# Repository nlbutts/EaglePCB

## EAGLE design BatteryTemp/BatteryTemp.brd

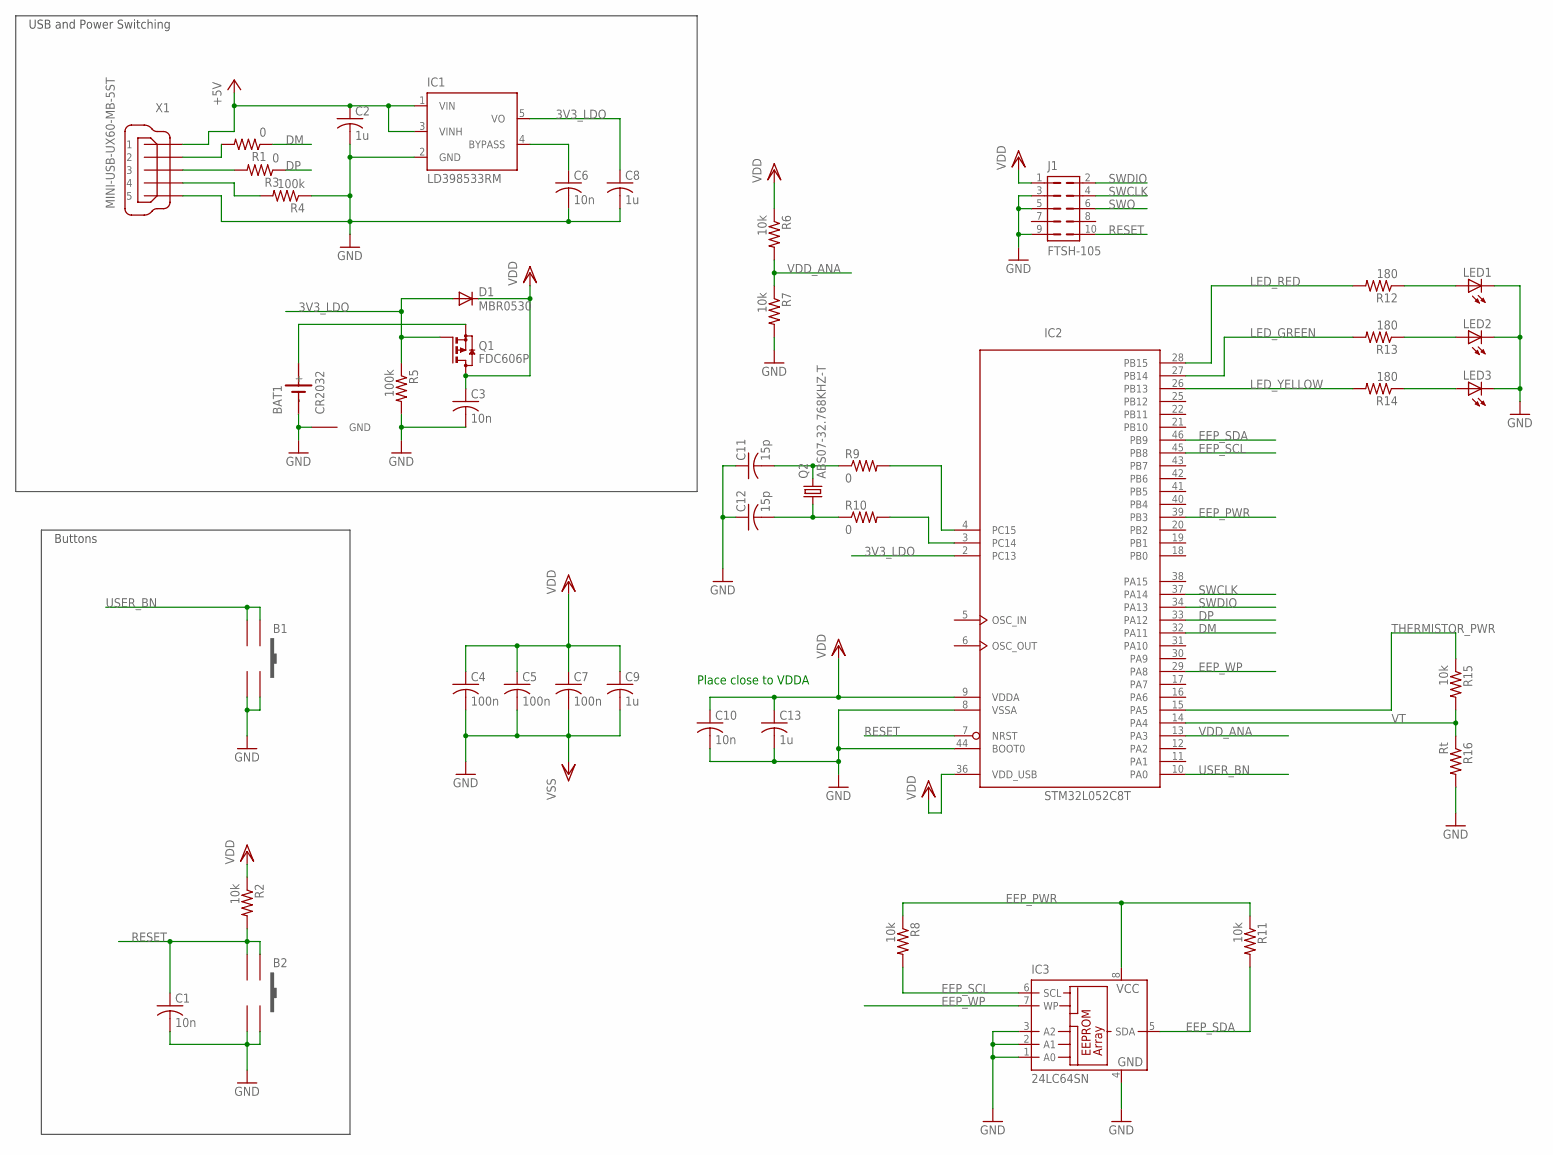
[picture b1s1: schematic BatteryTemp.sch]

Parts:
B1, B2: PTS525SM10SMTR; DIGIKEY CKN9104CT-ND
BAT1: CR2032; COIN_CELL; DIGIKEY BK-913-ND
C1, C3, C6: 10n; C0603
C2, C8, C9, C13: 1u; C0603
C4, C5, C7: 100n; C0603
C10: 10n; C0603; DIGIKEY 490-1512-1-ND
C11, C12: 15p; C0603
D1: MBR0530; SOD-123_MINI-SMA; DIGIKEY MBR0530TPMSCT-ND
IC1: LD398533RM; SOT23-5L; DIGIKEY 497-3504-1-ND
IC2: STM32L052C8T; LQFP48; DIGIKEY 497-14903-ND
IC3: 24LC64SN; SO-08
J1: FTSH-105; FTSH-105-01-XXX-DV-K; DIGIKEY SAM1161-50-ND
LED1: LEDCHIP-LED0603; CHIP-LED0603; DIGIKEY 475-2506-1-ND
LED2: LEDCHIP-LED0603; CHIP-LED0603; DIGIKEY 475-2709-1-ND
LED3: LEDCHIP-LED0603; CHIP-LED0603; DIGIKEY 475-1196-1-ND
Q1: FDC606P; SOT-23-6; DIGIKEY FDC606PCT-ND
Q2: ABS07-32.768KHZ-T; 2-SMD
R1, R3: 0; R0603; DIGIKEY P0.0GCT-ND
R2, R8, R11, R15: 10k; R0603
R4: 100k; R0603; DIGIKEY P100KGCT-ND
R5: 100k; R0603
R6, R7: 10k; R0603; DIGIKEY P10KYCT-ND
R9, R10: 0; R0603
R12: 180; R0603; DIGIKEY P180GCT-ND
R13, R14: 180; R0603
R16: Rt; R0603; DIGIKEY 490-2436-1-ND
T1: GND_LUG; GND_PAD
X1: MINI-USB-UX60-MB-5ST; UX60-MB-5ST; DIGIKEY H2959CT-ND

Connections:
3V3_LDO: C8.1, D1.A, IC1.5 (VO), IC2.2 (PC13), Q1.3 (G), R5.1
+5V: C2.1, IC1.1 (VIN), IC1.3 (VINH), X1.1
DM: IC2.32 (PA11), R1.1
DP: IC2.33 (PA12), R3.1
EEP_PWR: IC2.39 (PB3), IC3.8 (VCC), R8.1, R11.1
EEP_SCL: IC2.45 (PB8), IC3.6 (SCL), R8.2
EEP_SDA: IC2.46 (PB9), IC3.5 (SDA), R11.2
EEP_WP: IC2.29 (PA8), IC3.7 (WP)
GND: B1.3, B1.4, B2.3, B2.4, BAT1.GND1 (-), C1.2, C2.2, C3.2, C4.2, C5.2, C6.2, C7.2, C8.2, C9.2, C10.2, C11.1, C12.1, C13.2, IC1.2 (GND), IC2.8 (VSSA), IC2.23 (VSS), IC2.35 (VSS), IC2.44 (BOOT0), IC2.47 (VSS), IC3.1 (A0), IC3.2 (A1), IC3.3 (A2), IC3.4 (GND), J1.3, J1.5, J1.9, LED1.C, LED2.C, LED3.C, R4.1, R5.2, R7.2, R16.2, T1.P$1, X1.5
LED_GREEN: IC2.27 (PB14), R13.2
LED_RED: IC2.28 (PB15), R12.2
LED_YELLOW: IC2.26 (PB13), R14.2
unnamed: R1.2, X1.2
unnamed: R3.2, X1.3
unnamed: R4.2, X1.4
unnamed: BAT1.VPLUS1 (+), BAT1.VPLUS2 (+), Q1.4 (S)
unnamed: LED1.A, R12.1
unnamed: C6.1, IC1.4 (BYPASS)
unnamed: C11.2, Q2.P$2 (2), R9.1
unnamed: LED2.A, R13.1
unnamed: LED3.A, R14.1
unnamed: C12.2, Q2.P$1 (1), R10.1
unnamed: IC2.4 (PC15), R9.2
unnamed: IC2.3 (PC14), R10.2
RESET: B2.1, B2.2, C1.1, IC2.7 (NRST), J1.10, R2.2
SWCLK: IC2.37 (PA14), J1.4
SWDIO: IC2.34 (PA13), J1.2
SWO: J1.6
THERMISTOR_PWR: IC2.15 (PA5), R15.1
USER_BN: B1.1, B1.2, IC2.10 (PA0)
VDD: C3.1, C4.1, C5.1, C7.1, C9.1, C10.1, C13.1, D1.C, IC2.1 (VDD), IC2.9 (VDDA), IC2.24 (VDD), IC2.36 (VDD_USB), IC2.48 (VDD), J1.1, Q1.1 (D), Q1.2 (D), Q1.5 (D), Q1.6 (D), R2.1, R6.1
VDD_ANA: IC2.13 (PA3), R6.2, R7.1
VT: IC2.14 (PA4), R15.2, R16.1

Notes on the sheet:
Buttons
USB and Power Switching
Place close to VDDA

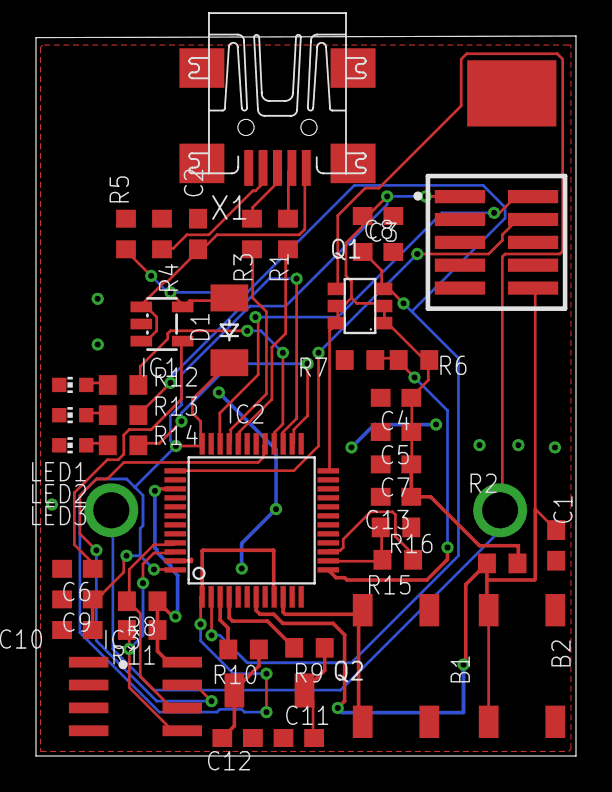
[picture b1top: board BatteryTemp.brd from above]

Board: 2 copper layers, 30.0 x 40.0 mm, 44 parts (1 on the bottom side), 32 nets.

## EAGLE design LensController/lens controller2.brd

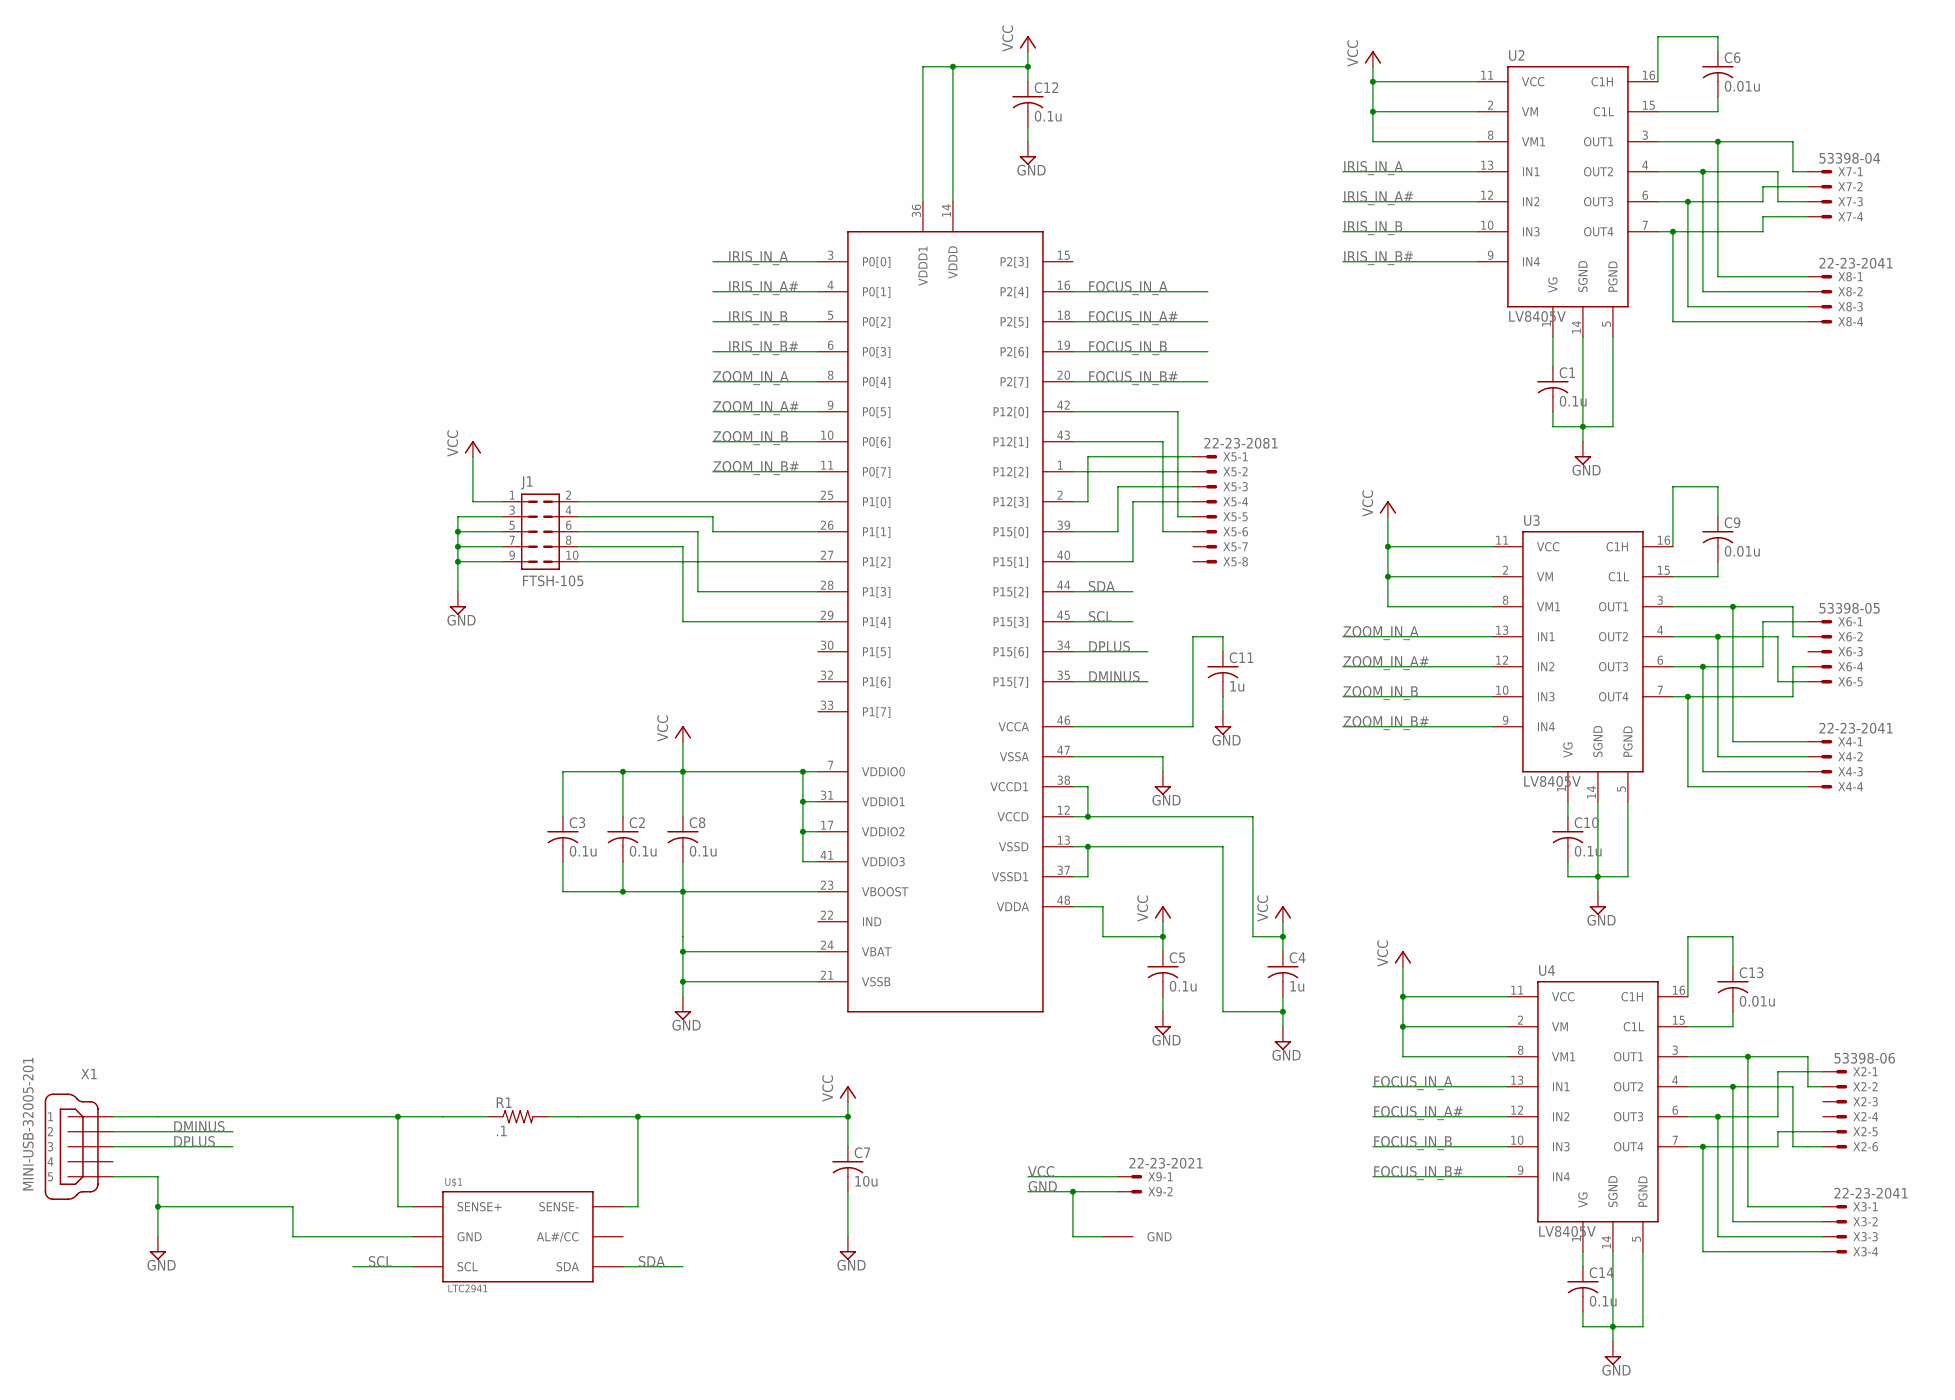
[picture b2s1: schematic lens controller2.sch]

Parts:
C1, C2, C3, C5, C8, C10, C12, C14: 0.1u; C1206
C4, C11: 1u; C1206
C6, C9, C13: 0.01u; C1206
C7: 10u; C1206
J1: FTSH-105; FTSH-105-01-XXX-DV-K
R1: .1; M1206
U1: CY8C3246PVI; SSOP48B
U2, U3, U4: LV8405V; SSOP16
U$1: LTC2941; DFN6-2X3
U$5: GND_LUG; GND_PAD
X1: MINI-USB-32005-201; 32005-201
X2: 53398-06
X3, X4, X8: 22-23-2041
X5: 22-23-2081
X6: 53398-05
X7: 53398-04
X9: 22-23-2021

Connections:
DMINUS: U1.35 (P15[7]), X1.2
DPLUS: U1.34 (P15[6]), X1.3
FOCUS_IN_A: U1.16 (P2[4]), U4.13 (IN1)
FOCUS_IN_A#: U1.18 (P2[5]), U4.12 (IN2)
FOCUS_IN_B: U1.19 (P2[6]), U4.10 (IN3)
FOCUS_IN_B#: U1.20 (P2[7]), U4.9 (IN4)
GND: C1.2, C2.2, C3.2, C4.2, C5.2, C7.2, C8.2, C10.2, C11.2, C12.2, C14.2, J1.3, J1.5, J1.7, J1.9, U1.13 (VSSD), U1.21 (VSSB), U1.23 (VBOOST), U1.24 (VBAT), U1.37 (VSSD1), U1.47 (VSSA), U2.5 (PGND), U2.14 (SGND), U3.5 (PGND), U3.14 (SGND), U4.5 (PGND), U4.14 (SGND), U$1.2 (GND), U$5.P$1, X1.5, X9.2
IRIS_IN_A: U1.3 (P0[0]), U2.13 (IN1)
IRIS_IN_A#: U1.4 (P0[1]), U2.12 (IN2)
IRIS_IN_B: U1.5 (P0[2]), U2.10 (IN3)
IRIS_IN_B#: U1.6 (P0[3]), U2.9 (IN4)
unnamed: J1.2, U1.25 (P1[0])
unnamed: J1.4, U1.26 (P1[1])
unnamed: J1.10, U1.27 (P1[2])
unnamed: J1.6, U1.28 (P1[3])
unnamed: J1.8, U1.29 (P1[4])
unnamed: C11.1, U1.46 (VCCA)
unnamed: C6.2, U2.15 (C1L)
unnamed: C6.1, U2.16 (C1H)
unnamed: C1.1, U2.1 (VG)
unnamed: C9.2, U3.15 (C1L)
unnamed: C9.1, U3.16 (C1H)
unnamed: C10.1, U3.1 (VG)
unnamed: U2.3 (OUT1), X7.1, X8.1
unnamed: U2.4 (OUT2), X7.3, X8.2
unnamed: C13.2, U4.15 (C1L)
unnamed: C13.1, U4.16 (C1H)
unnamed: C14.1, U4.1 (VG)
unnamed: U2.6 (OUT3), X7.2, X8.3
unnamed: U2.7 (OUT4), X7.4, X8.4
unnamed: U3.3 (OUT1), X4.1, X6.2
unnamed: U3.4 (OUT2), X4.2, X6.5
unnamed: U3.6 (OUT3), X4.3, X6.1
unnamed: U3.7 (OUT4), X4.4, X6.4
unnamed: U4.3 (OUT1), X2.2, X3.1
unnamed: U4.4 (OUT2), X2.6, X3.2
unnamed: U4.6 (OUT3), X2.1, X3.3
unnamed: U4.7 (OUT4), X2.5, X3.4
unnamed: U1.43 (P12[1]), X5.6
unnamed: U1.42 (P12[0]), X5.5
unnamed: U1.40 (P15[1]), X5.4
unnamed: U1.39 (P15[0]), X5.3
unnamed: U1.2 (P12[3]), X5.1
unnamed: U1.1 (P12[2]), X5.2
unnamed: R1.1, U$1.1 (SENSE+), X1.1
SCL: U1.45 (P15[3]), U$1.3 (SCL)
SDA: U1.44 (P15[2]), U$1.4 (SDA)
VCC: C2.1, C3.1, C4.1, C5.1, C7.1, C8.1, C12.1, J1.1, R1.2, U1.7 (VDDIO0), U1.12 (VCCD), U1.14 (VDDD), U1.17 (VDDIO2), U1.31 (VDDIO1), U1.36 (VDDD1), U1.38 (VCCD1), U1.41 (VDDIO3), U1.48 (VDDA), U2.2 (VM), U2.8 (VM1), U2.11 (VCC), U3.2 (VM), U3.8 (VM1), U3.11 (VCC), U4.2 (VM), U4.8 (VM1), U4.11 (VCC), U$1.6 (SENSE-), X9.1
ZOOM_IN_A: U1.8 (P0[4]), U3.13 (IN1)
ZOOM_IN_A#: U1.9 (P0[5]), U3.12 (IN2)
ZOOM_IN_B: U1.10 (P0[6]), U3.10 (IN3)
ZOOM_IN_B#: U1.11 (P0[7]), U3.9 (IN4)

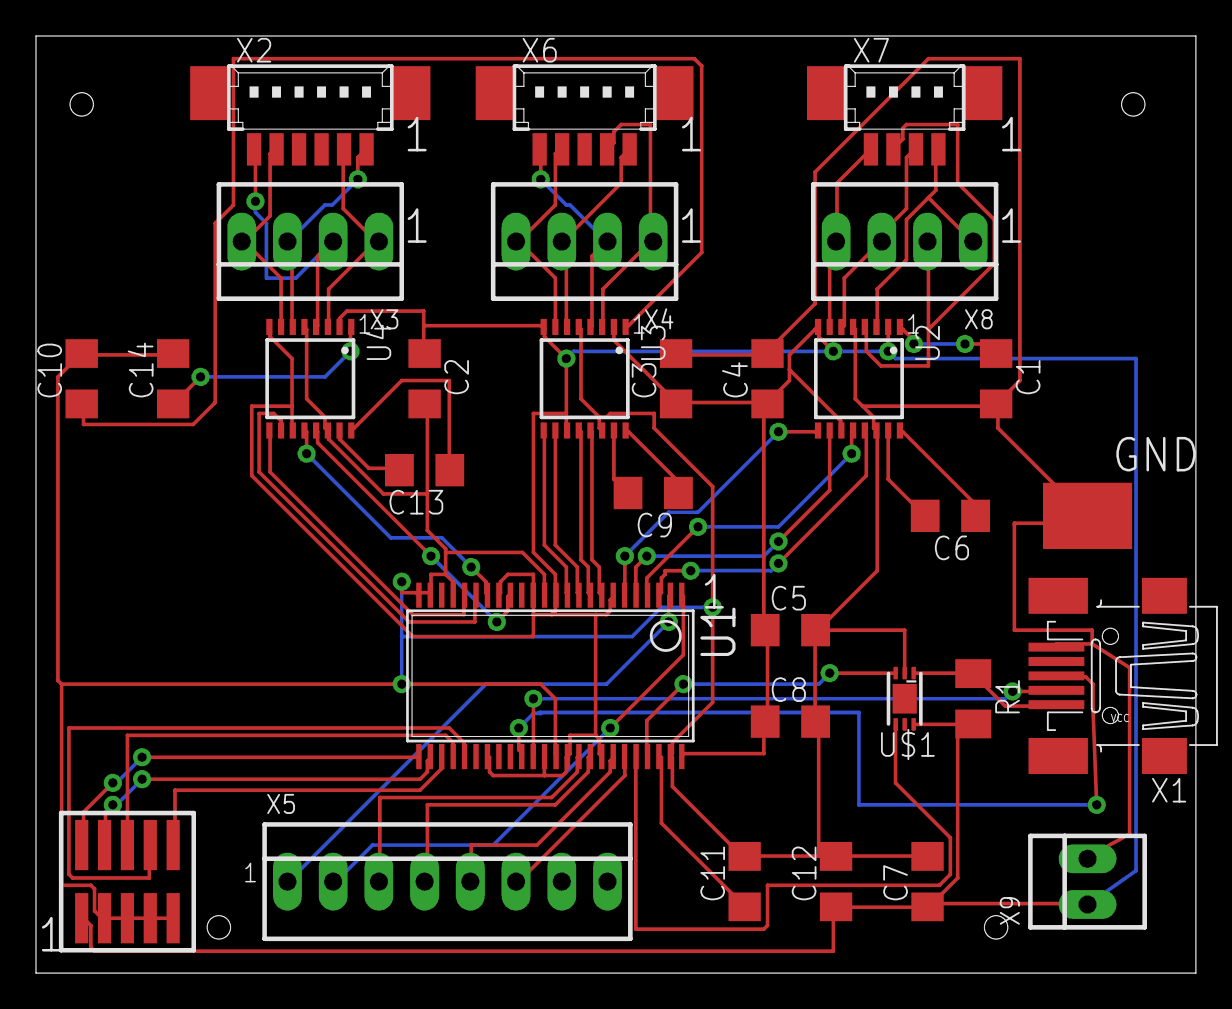
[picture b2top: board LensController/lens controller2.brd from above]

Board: 2 copper layers, 64.4 x 52.1 mm, 31 parts (0 on the bottom side), 52 nets.

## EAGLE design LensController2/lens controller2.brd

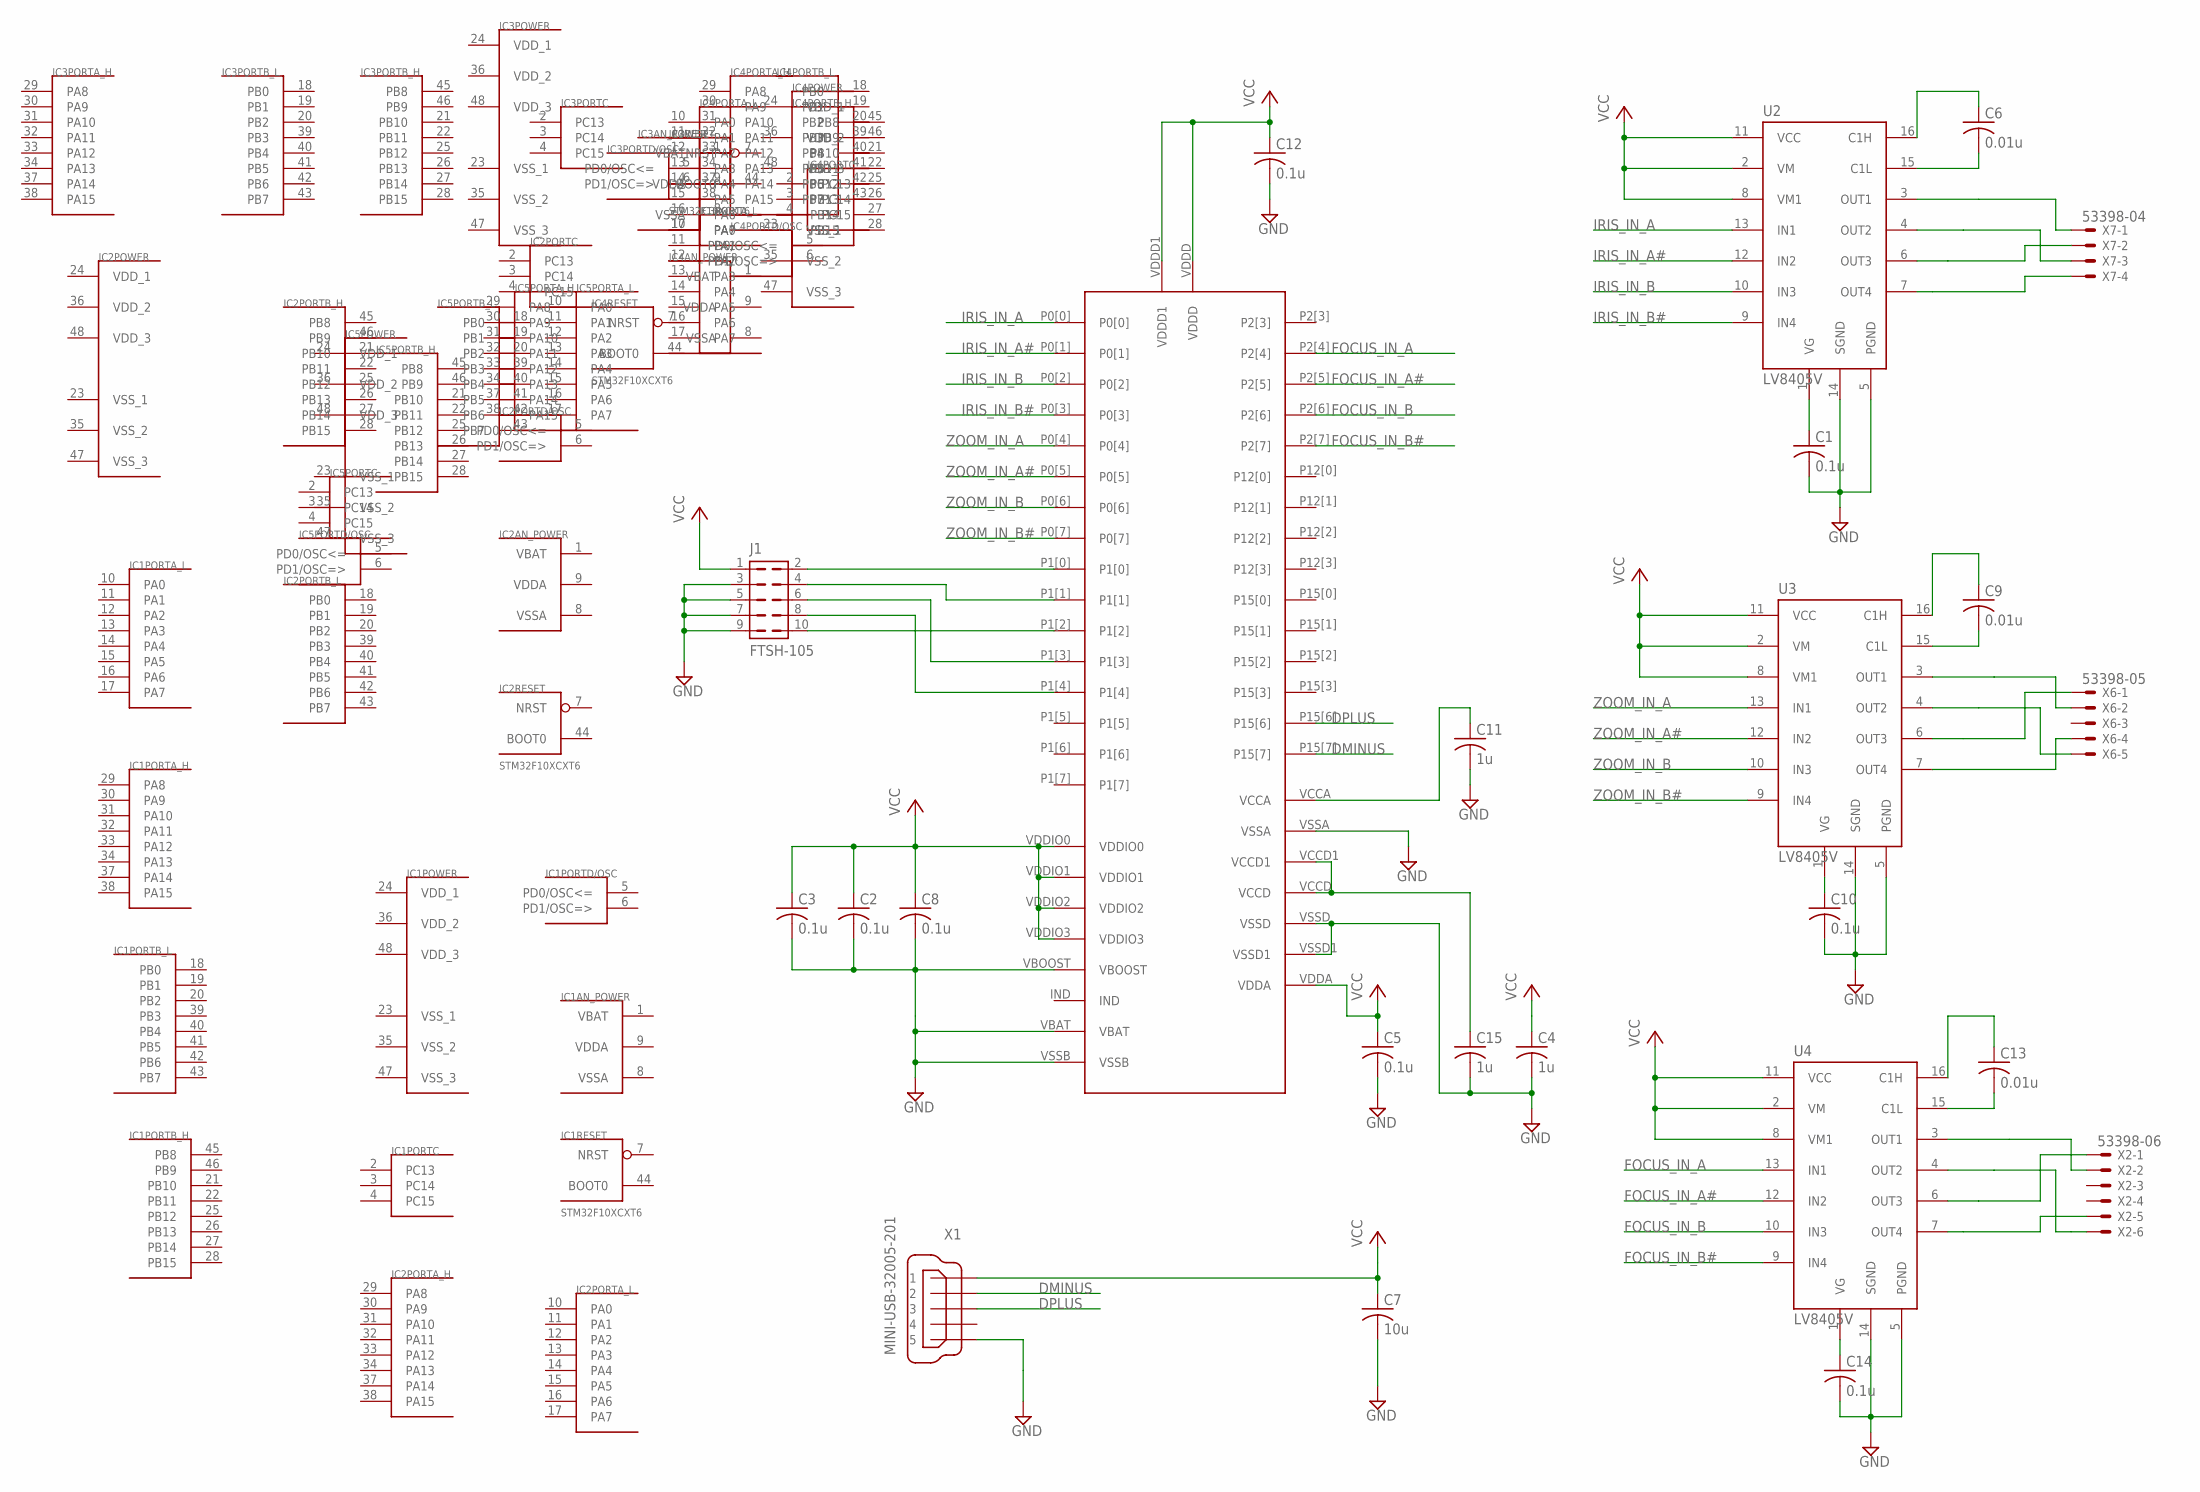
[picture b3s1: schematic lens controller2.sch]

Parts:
C1, C2, C3, C5, C8, C10, C12, C14: 0.1u; C1206
C4, C11, C15: 1u; C1206
C6, C9, C13: 0.01u; C1206
C7: 10u; C1206
IC1, IC2, IC3, IC4, IC5: STM32F10XCXT6; TQFP48
J1: FTSH-105; FTSH-105-01-XXX-DV-K
U1: CY8C3XXX_48QFN; 48QFN
U2, U3, U4: LV8405V; SSOP16
X1: MINI-USB-32005-201; 32005-201
X2: 53398-06
X6: 53398-05
X7: 53398-04

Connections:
DMINUS: U1.P15[7], X1.2
DPLUS: U1.P15[6], X1.3
FOCUS_IN_A: U1.P2[4], U4.13 (IN1)
FOCUS_IN_A#: U1.P2[5], U4.12 (IN2)
FOCUS_IN_B: U1.P2[6], U4.10 (IN3)
FOCUS_IN_B#: U1.P2[7], U4.9 (IN4)
GND: C1.2, C2.2, C3.2, C4.2, C5.2, C7.2, C8.2, C10.2, C11.2, C12.2, C14.2, C15.2, J1.3, J1.5, J1.7, J1.9, U1.VBAT, U1.VBOOST, U1.VSSA, U1.VSSB, U1.VSSD, U1.VSSD1, U2.5 (PGND), U2.14 (SGND), U3.5 (PGND), U3.14 (SGND), U4.5 (PGND), U4.14 (SGND), X1.5
IRIS_IN_A: U1.P0[0], U2.13 (IN1)
IRIS_IN_A#: U1.P0[1], U2.12 (IN2)
IRIS_IN_B: U1.P0[2], U2.10 (IN3)
IRIS_IN_B#: U1.P0[3], U2.9 (IN4)
unnamed: J1.2, U1.P1[0]
unnamed: J1.4, U1.P1[1]
unnamed: J1.10, U1.P1[2]
unnamed: J1.6, U1.P1[3]
unnamed: J1.8, U1.P1[4]
unnamed: C11.1, U1.VCCA
unnamed: C6.2, U2.15 (C1L)
unnamed: C6.1, U2.16 (C1H)
unnamed: C1.1, U2.1 (VG)
unnamed: C9.2, U3.15 (C1L)
unnamed: C9.1, U3.16 (C1H)
unnamed: C10.1, U3.1 (VG)
unnamed: U2.3 (OUT1), X7.1
unnamed: U2.4 (OUT2), X7.3
unnamed: C13.2, U4.15 (C1L)
unnamed: C13.1, U4.16 (C1H)
unnamed: C14.1, U4.1 (VG)
unnamed: U2.6 (OUT3), X7.2
unnamed: U2.7 (OUT4), X7.4
unnamed: U3.3 (OUT1), X6.2
unnamed: U3.4 (OUT2), X6.5
unnamed: U3.6 (OUT3), X6.1
unnamed: U3.7 (OUT4), X6.4
unnamed: U4.3 (OUT1), X2.2
unnamed: U4.4 (OUT2), X2.6
unnamed: U4.6 (OUT3), X2.1
unnamed: U4.7 (OUT4), X2.5
unnamed: C15.1, U1.VCCD, U1.VCCD1
unnamed: IC3.10 (PA0), IC4.17 (PA7)
unnamed: IC3.5 (PD0/OSC<=), IC4.34 (PA13)
unnamed: IC3.6 (PD1/OSC=>), IC4.37 (PA14)
VBAT: IC1.1 (VBAT), IC2.1 (VBAT), IC3.1 (VBAT), IC4.1 (VBAT), IC5.1 (VBAT)
VCC: C2.1, C3.1, C4.1, C5.1, C7.1, C8.1, C12.1, J1.1, U1.VDDA, U1.VDDD, U1.VDDD1, U1.VDDIO0, U1.VDDIO1, U1.VDDIO2, U1.VDDIO3, U2.2 (VM), U2.8 (VM1), U2.11 (VCC), U3.2 (VM), U3.8 (VM1), U3.11 (VCC), U4.2 (VM), U4.8 (VM1), U4.11 (VCC), X1.1
VDDA: IC1.9 (VDDA), IC2.9 (VDDA), IC3.9 (VDDA), IC4.9 (VDDA), IC5.9 (VDDA)
VDD_1: IC1.24 (VDD_1), IC2.24 (VDD_1), IC3.24 (VDD_1), IC4.24 (VDD_1), IC5.24 (VDD_1)
VDD_2: IC1.36 (VDD_2), IC2.36 (VDD_2), IC3.36 (VDD_2), IC4.36 (VDD_2), IC5.36 (VDD_2)
VDD_3: IC1.48 (VDD_3), IC2.48 (VDD_3), IC3.48 (VDD_3), IC4.48 (VDD_3), IC5.48 (VDD_3)
VSSA: IC1.8 (VSSA), IC2.8 (VSSA), IC3.8 (VSSA), IC4.8 (VSSA), IC5.8 (VSSA)
VSS_1: IC1.23 (VSS_1), IC2.23 (VSS_1), IC3.23 (VSS_1), IC4.23 (VSS_1), IC5.23 (VSS_1)
VSS_2: IC1.35 (VSS_2), IC2.35 (VSS_2), IC3.35 (VSS_2), IC4.35 (VSS_2), IC5.35 (VSS_2)
VSS_3: IC1.47 (VSS_3), IC2.47 (VSS_3), IC3.47 (VSS_3), IC4.47 (VSS_3), IC5.47 (VSS_3)
ZOOM_IN_A: U1.P0[4], U3.13 (IN1)
ZOOM_IN_A#: U1.P0[5], U3.12 (IN2)
ZOOM_IN_B: U1.P0[6], U3.10 (IN3)
ZOOM_IN_B#: U1.P0[7], U3.9 (IN4)

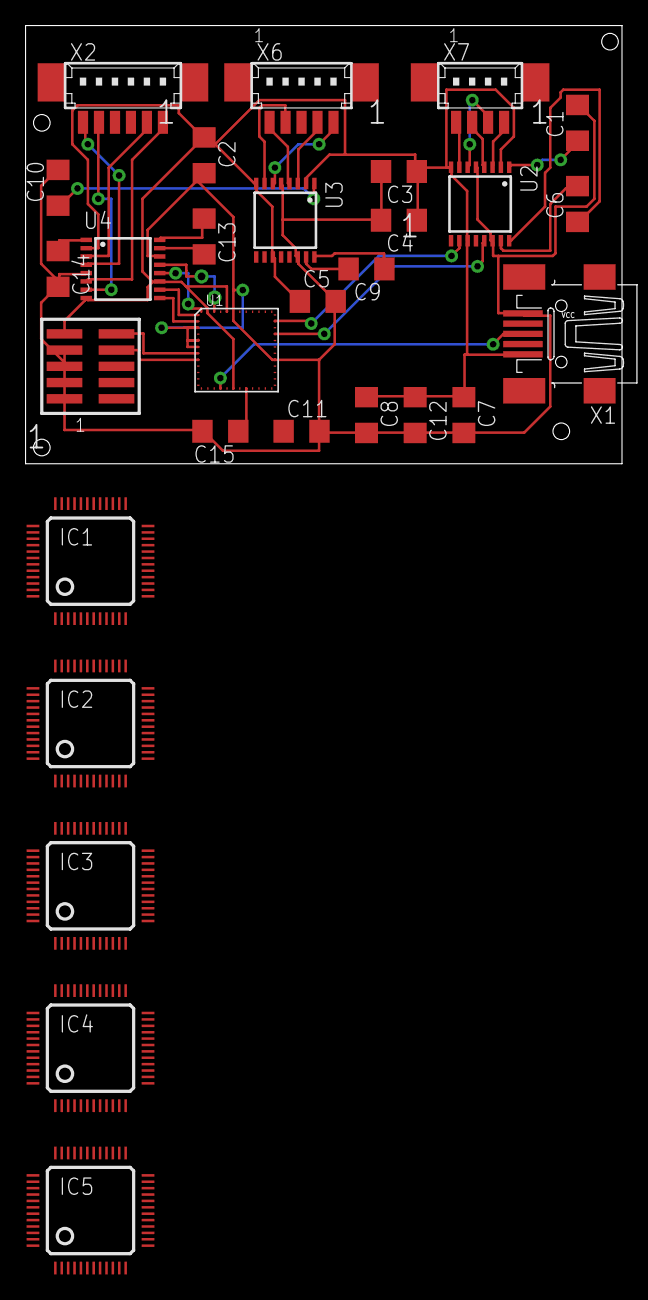
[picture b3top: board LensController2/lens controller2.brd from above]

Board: 2 copper layers, 46.7 x 34.3 mm, 29 parts (0 on the bottom side), 56 nets.

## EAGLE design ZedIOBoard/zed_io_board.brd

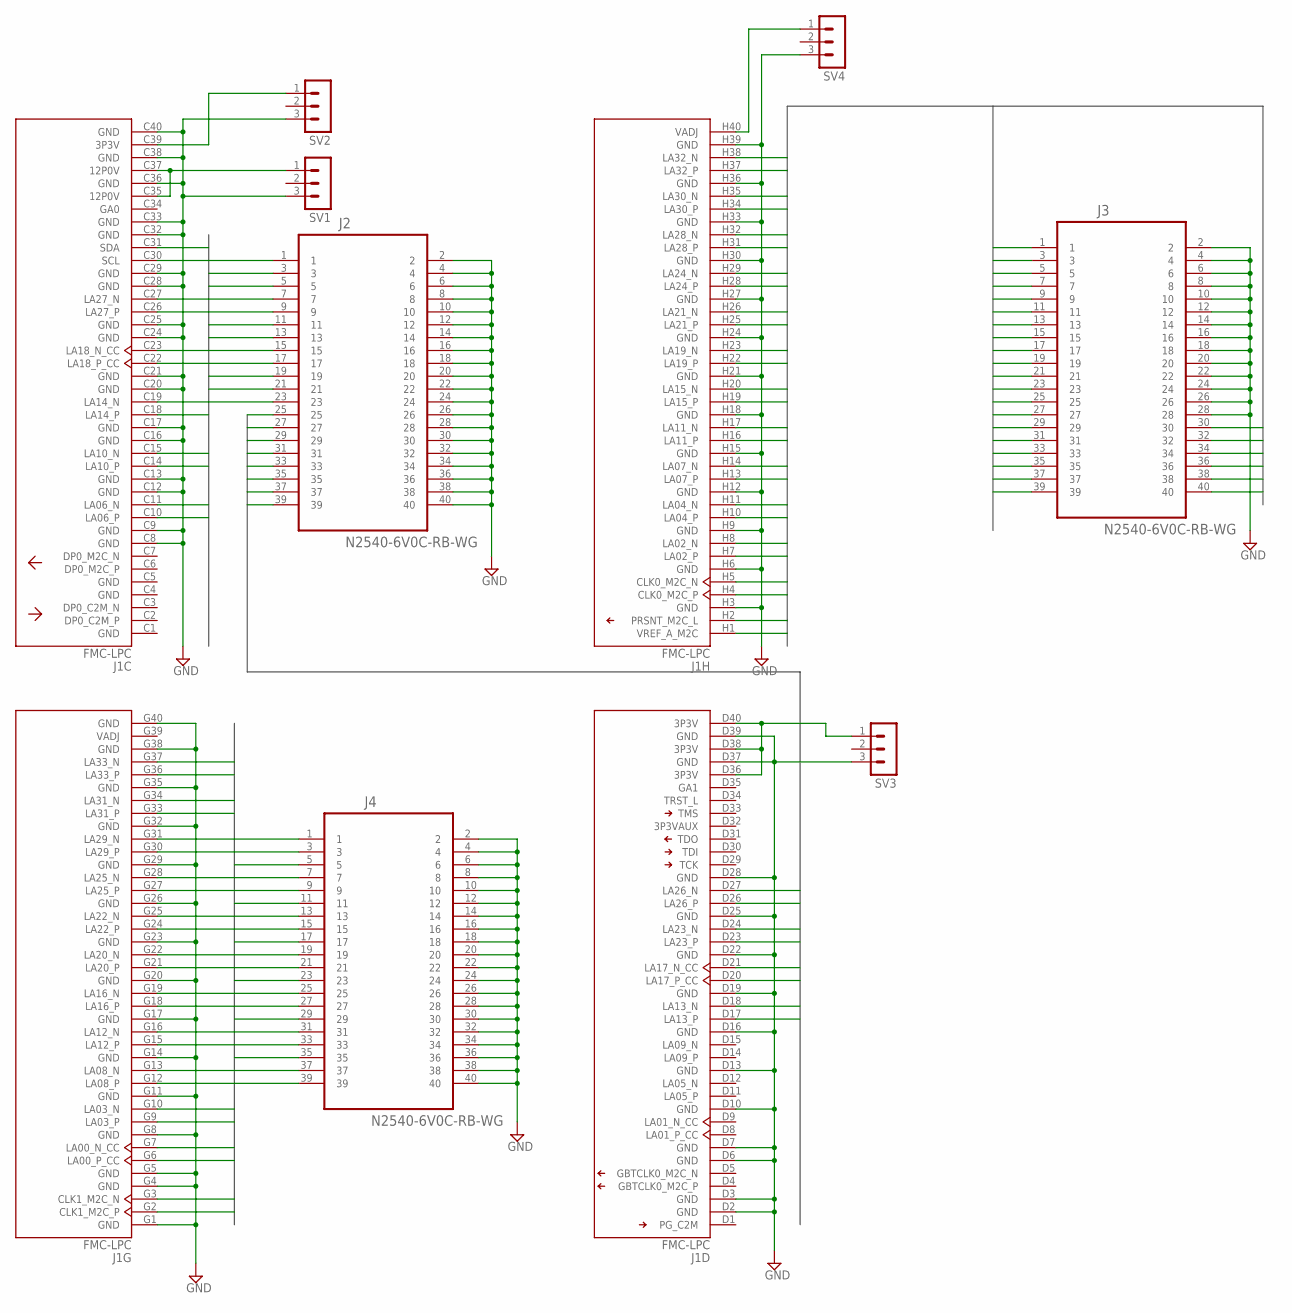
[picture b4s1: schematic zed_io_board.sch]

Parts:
J1: FMC-LPC; FMC-LPC-MALE
J2, J3, J4: N2540-6V0C-RB-WG
SV1, SV2, SV3, SV4: MA03-1

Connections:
BA1: J1.H38 (LA32_N), J3.1
BA2: J1.H37 (LA32_P), J3.3
BA3: J1.H35 (LA30_N), J3.5
BA4: J1.H34 (LA30_P), J3.7
BA5: J1.H32 (LA28_N), J3.9
BA6: J1.H31 (LA28_P), J3.11
BA7: J1.H29 (LA24_N), J3.13
BA8: J1.H28 (LA24_P), J3.15
BA9: J1.H26 (LA21_N), J3.17
BA10: J1.H25 (LA21_P), J3.19
BA11: J1.H23 (LA19_N), J3.21
BA12: J1.H22 (LA19_P), J3.23
BA13: J1.H20 (LA15_N), J3.25
BA14: J1.H19 (LA15_P), J3.27
BA15: J1.H17 (LA11_N), J3.29
BA16: J1.H16 (LA11_P), J3.31
BA17: J1.H14 (LA07_N), J3.33
BA18: J1.H13 (LA07_P), J3.35
BA19: J1.H11 (LA04_N), J3.37
BA20: J1.H10 (LA04_P), J3.39
BA21: J1.H8 (LA02_N), J3.30
BA22: J1.H7 (LA02_P), J3.32
BA23: J1.H5 (CLK0_M2C_N), J3.34
BA24: J1.H4 (CLK0_M2C_P), J3.36
BA25: J1.H2 (PRSNT_M2C_L), J3.38
BA26: J1.H1 (VREF_A_M2C), J3.40
BB1: J1.C31 (SDA), J2.1
BB2: J1.C30 (SCL), J2.3
BB3: J1.C27 (LA27_N), J2.5
BB4: J1.C26 (LA27_P), J2.7
BB5: J1.C23 (LA18_N_CC), J2.9
BB6: J1.C22 (LA18_P_CC), J2.11
BB7: J1.C19 (LA14_N), J2.13
BB8: J1.C18 (LA14_P), J2.15
BB9: J1.C15 (LA10_N), J2.17
BB10: J1.C14 (LA10_P), J2.19
BB11: J1.C11 (LA06_N), J2.21
BB12: J1.C10 (LA06_P), J2.23
BD1: J1.D27 (LA26_N), J2.25
BD2: J1.D26 (LA26_P), J2.27
BD3: J1.D24 (LA23_N), J2.29
BD4: J1.D23 (LA23_P), J2.31
BD5: J1.D21 (LA17_N_CC), J2.33
BD6: J1.D20 (LA17_P_CC), J2.35
BD7: J1.D18 (LA13_N), J2.37
BD8: J1.D17 (LA13_P), J2.39
BG1: J1.G37 (LA33_N), J4.1
BG2: J1.G36 (LA33_P), J4.3
BG3: J1.G34 (LA31_N), J4.5
BG4: J1.G33 (LA31_P), J4.7
BG5: J1.G31 (LA29_N), J4.9
BG6: J1.G30 (LA29_P), J4.11
BG7: J1.G28 (LA25_N), J4.13
BG8: J1.G27 (LA25_P), J4.15
BG9: J1.G25 (LA22_N), J4.17
BG10: J1.G24 (LA22_P), J4.19
BG11: J1.G22 (LA20_N), J4.21
BG12: J1.G21 (LA20_P), J4.23
BG13: J1.G19 (LA16_N), J4.25
BG14: J1.G18 (LA16_P), J4.27
BG15: J1.G16 (LA12_N), J4.29
BG16: J1.G15 (LA12_P), J4.31
BG17: J1.G13 (LA08_N), J4.33
BG18: J1.G12 (LA08_P), J4.35
BG19: J1.G10 (LA03_N), J4.37
BG20: J1.G9 (LA03_P), J4.39
BG21: J1.G7 (LA00_N_CC)
BG22: J1.G6 (LA00_P_CC)
BG23: J1.G3 (CLK1_M2C_N)
BG24: J1.G2 (CLK1_M2C_P)
GND: J1.C8 (GND), J1.C9 (GND), J1.C12 (GND), J1.C13 (GND), J1.C16 (GND), J1.C17 (GND), J1.C20 (GND), J1.C21 (GND), J1.C24 (GND), J1.C25 (GND), J1.C28 (GND), J1.C29 (GND), J1.C32 (GND), J1.C33 (GND), J1.C36 (GND), J1.C38 (GND), J1.C40 (GND), J1.D2 (GND), J1.D3 (GND), J1.D6 (GND), J1.D7 (GND), J1.D10 (GND), J1.D13 (GND), J1.D16 (GND), J1.D19 (GND), J1.D22 (GND), J1.D25 (GND), J1.D28 (GND), J1.D37 (GND), J1.D39 (GND), J1.G1 (GND), J1.G4 (GND), J1.G5 (GND), J1.G8 (GND), J1.G11 (GND), J1.G14 (GND), J1.G17 (GND), J1.G20 (GND), J1.G23 (GND), J1.G26 (GND), J1.G29 (GND), J1.G32 (GND), J1.G35 (GND), J1.G38 (GND), J1.G40 (GND), J1.H3 (GND), J1.H6 (GND), J1.H9 (GND), J1.H12 (GND), J1.H15 (GND), J1.H18 (GND), J1.H21 (GND), J1.H24 (GND), J1.H27 (GND), J1.H30 (GND), J1.H33 (GND), J1.H36 (GND), J1.H39 (GND), J2.2, J2.4, J2.6, J2.8, J2.10, J2.12, J2.14, J2.16, J2.18, J2.20, J2.22, J2.24, J2.26, J2.28, J2.30, J2.32, J2.34, J2.36, J2.38, J2.40, J3.2, J3.4, J3.6, J3.8, J3.10, J3.12, J3.14, J3.16, J3.18, J3.20, J3.22, J3.24, J3.26, J3.28, J4.2, J4.4, J4.6, J4.8, J4.10, J4.12, J4.14, J4.16, J4.18, J4.20, J4.22, J4.24, J4.26, J4.28, J4.30, J4.32, J4.34, J4.36, J4.38, J4.40, SV1.3, SV2.3, SV3.3, SV4.3
unnamed: J1.C39 (3P3V), SV2.1
unnamed: J1.C35 (12P0V), J1.C37 (12P0V), SV1.1
unnamed: J1.H40 (VADJ), SV4.1
unnamed: J1.D36 (3P3V), J1.D38 (3P3V), J1.D40 (3P3V), SV3.1

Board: 2 copper layers, 8 parts (0 on the bottom side), 71 nets, no tracks yet.
